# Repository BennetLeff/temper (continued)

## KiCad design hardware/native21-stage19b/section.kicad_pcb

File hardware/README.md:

# Current Temper hardware

The current engineering candidate is **native-21 stage19b**, the full-bridge
power stage. Open [the pinned KiCad project](native21-stage19b/section.kicad_pro).
It is a **digital candidate, not a fabrication or mains-operation release**.

Before a current-design review, run:

```sh
make hardware-baseline-check
sh scripts/check_hardware_baseline.sh --board hardware/native21-stage19b/section.kicad_pcb
```

[CURRENT.tsv](CURRENT.tsv) pins the exact board, schematic, project, rules,
libraries, source inputs and source evidence. The Rust guard rejects missing,
changed, malformed or ambiguous inputs and any selected board whose full hash
differs. A successful check establishes identity only. It does not certify the
design or prove that an edited producer worktree still matches this snapshot.

| Identity | Value |
|---|---|
| Board SHA-256 | `b19a45530bb0f39d2d3c0412e3774b6d5a47c4238d3fee867790cce410756662` |
| Authored copper (`provenance/copper.json`) | `ce49f20024545fe28f104e72f69c0d1362227a15145b3a1c3bd4b915199b6cf2`, the reproducible identity: rebuilds of the same copper differ in KiCad UUIDs and timestamps |
| Schematic | `e6993fa4abab0a845d1cc0d07074c39ab9f536eca6f864dae993d76941ae8d35` |
| Frozen netlist (`provenance/default.net`) | `8a7e1c4a869445d7d11ab9ee4c69f0dc40207cf4f06463a0ac8b2238cffef92b` |
| Stage 19b hardware commit | `5d53896c3` on `codex/power-stage-integration` (tag `native21s19b`; 357 parts). Carries stage 17b (Bourns CSS2H R5), stage 18 (RES_A 12.6 mm outer-layer spacing) and stage 19 (review N1/K6 bypass and DRC fixes from `365151b62`, PI1/PI2 local caps at U41/U42/U26, SI1/SI2 return paths, C153–C156) |
| Superseded | stage15b `9a9c43c6…` (hardware commit `d5b1e9995504f1ee7b6439a57f998d73125b3352`), stage 16 `e9481ed6…`, stage 17b `96501e7d…`, the integration stage 18 `3768a126…`, and the review-fix side builds `dadcaad3…` and `98fa8bee…` (branches `claude/native21-stage17-review` / `claude/native21-stage18-review`, folded into stage 19); the guard rejects all of them |

## Source ownership and updates

The source owner is branch `codex/power-stage-integration`, unit
`zapote/power-stage-120v/`; stage 19b is merged there at `5d53896c3`. Atopile entry:
`elec/src/power_stage_120v.ato:PowerStage120V`. Its `native-21/layout/copper.json`
and `native-21/verification/final-manifest.json` define the routed candidate.
Do not edit this snapshot to make a check pass. Make design changes in the
owning sources, regenerate and review them, then deliberately publish a new
snapshot and update CURRENT.tsv together, retaining the previous identity here.
Compare live producer source hashes to the snapshot before reusing its results.

The routed board was built from the committed `copper.json` by
`sh native-21/layout/incr_iter.sh native-21/layout/copper.json - OUTDIR`
(`native-21/layout/gates/chain.sh`). Its `source/` directory is provenance, not a
second editable source of truth.

## Superseded inputs and filename traps

| Location | Status |
|---|---|
| Legacy half-bridge `pcb/`, root `elec/` | Removed from main on 2026-10-08; recoverable from tag `archive/temper-legacy-2026-10-08`. Never the current design |
| `native-21/section.kicad_pcb` in the producer | Placement-only build input, not the routed board |
| `native-21/routed/section.kicad_pcb` in the producer | Stale October 7 output; not stage19b |
| Enclosure `inputs/native-21/` snapshots | Independently versioned; check the hash before reuse (R38's was stage12) |
| Stage15b through stage 18 boards, the review-fix side builds, and the engineering review's findings | The review (`output/engineering-review-native21-stage15b-2026-10-11/REPORT.md`) names stage15b; its addendum covers the side build. Stage 19's results are in `zapote/power-stage-120v/DECISIONS.md` item 19 at `5d53896c3` |

Do not transfer component references, topology, spacing limits, firmware
thresholds or a readiness verdict between these designs. All future reports
must name the manifest and full selected PCB hash before interpreting findings.

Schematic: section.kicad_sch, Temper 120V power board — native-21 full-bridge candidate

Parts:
BR1: GBJ2510-F; Diode_Bridge_GBJ2510
C1, C2: R463N410050N1K; KEMET_R463N410000N1M_P22.50_ReviewOnly
C3, C4: DE1E3RA222MA4BP01F; Murata_DE1E3RA222MA4BP01F_P10.0_Pad1.5_ReviewOnly
C5, C6: B32676G1905K000; TDK_B32656G0275J000_4Pin_P37.50_P20.30_ReviewOnly
C7, C14, C25, C28, C29, C32, C34, C35, C36, C37, C44, C45, C46, C47, C48, C49, C54, C61, C65, C70, C74, C75, C80, C81, C82, C87, C88, C89, C131, C133, C134, C135, C137, C138, C139, C141, C142, C144, C153, C154, C155, C156: CC0603KRX7R9BB104; C_0603_1608Metric
C8, C10, C15, C17: CC0805KRX7R9BB104; C_0805_2012Metric
C9, C16, C24, C26, C90, C91, C92, C93, C94, C95, C96, C97, C98, C99, C100, C102, C103, C104, C106, C107, C108, C132, C136, C140: UMK325AB7106KM-T; C_1210_3225Metric
C11, C18: GRM21BZ71E106KE15L; C_0805_2012Metric
C12, C13, C19, C20: GRM31A5C3A102JW01D; C_1206_3216Metric
C21, C22, C23, C151, C152: B32654A1104K000; TDK_B32654_P27.5_W14.0_L31.5_Radial
C27, C31, C33, C55, C56, C62, C63, C66, C67, C68, C69, C76, C77, C78, C79, C83, C84, C85, C86, C143: C0603C102J5GACTU; C_0603_1608Metric
C30: CL10C101JB8NNNC; C_0603_1608Metric
C38, C39, C40, C41: B32652A0104K000; TDK_B32652A0104K000_P15.00_ReviewOnly
C42, C43: GRM31C5C1H104JA01L; C_1206_3216Metric
C50, C51, C52, C53, C57, C58, C59, C60, C64: GRM188R71E105KA12D; C_0603_1608Metric
C71, C72, C105, C109: CL10C331JB8NNNC; C_0603_1608Metric
C110, C111, C112, C113, C114, C115, C116, C117, C118, C119, C120, C121, C122, C123, C124, C125: CL05B104KB54PNC; C_0402_1005Metric
C126, C127, C128, C129: 6SVPC220M; CP_Elec_6.3x5.9
C145, C146, C147, C148, C149, C150: CL21B105KBFNNNE; C_0805_2012Metric
D3, D17: 30KPA150CA; P600_Axial_P12.70mm_ReviewOnly
D4, D5: BAS116H,115; D_SOD-123F
D6, D7, D8, D9: PMEG6030EP,115; D_SOD-128
D14, D15, D16: 1N4148W; D_SOD-123
F1: KLDR025.TXP; Fuseholder_Clip-10.3x38mm_Littelfuse_125_Inline_P41.76x10.8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
F2: 3403.0171; Fuse_Schurter_UMT250
J1: 1711725; TerminalBlock_Phoenix_MKDS-3-2-5.08_1x02_P5.08mm_Horizontal
J2, J5, J7, J8, J9, J10: 74650074; Wuerth_REDCUBE-THR_WP-THRBU_74650074_THR
J3, J11: B2P3-VH(LF)(SN); JST_VH_B2P3-VH_1x02_P7.92mm_Vertical
J4: 0430451612; Molex_Micro-Fit_3.0_43045-1612_2x08_P3.00mm_Vertical
J6: 1704004; Phoenix_KDS3_1704004_1Pos_2Pin_ReviewOnly
L1: B82726S2203A020; B82726S2_ReviewOnly
PS1: IRM-20-15; Converter_ACDC_MeanWell_IRM-20-xx_THT
PS2: IRM-20-24; Converter_ACDC_MeanWell_IRM-20-xx_THT
Q1, Q4: AO3400A; SOT-23
Q2, Q3, Q5, Q6: IPW65R018CFD7; TO-247-3_Vertical
Q7, Q8, Q9: MMBT3904; SOT-23
R1, R2: 1206W4F1003T5E; R_1206_3216Metric
R3, R4: RC1206FR-07220KL; R_1206_3216Metric
R5: CSS2H-2512R-1L00F; R_Shunt_Bourns_CSS2H-2512_Kelvin
R6, R14: 0603WAF1000T5E; R_0603_1608Metric
R7, R15, R62, R128: 0603WAF1003T5E; R_0603_1608Metric
R8, R16: 0603WAF3300T5E; R_0603_1608Metric
R9, R17: RT0603BRD0749K9L; R_0603_1608Metric
R10, R12, R18, R20: RC1206FR-073R9L; R_1206_3216Metric
R11, R13, R19, R21, R73, R76, R90, R91, R108, R109, R123, R124, R126: 0603WAF1002T5E; R_0603_1608Metric
R22, R23, R24, R25, R26, R27, R28, R29: RC1206FR-07470KL; R_1206_3216Metric
R30: RT0603BRD0715K8L; R_0603_1608Metric
R31: 0603WAF5601T5E; R_0603_1608Metric
R32, R33, R36, R44, R45, R49, R50, R78, R79, R80, R82, R84, R86, R88, R96, R97, R98, R100, R102, R104, R106, R111, R112, R113, R115, R117, R119, R121: RT0603BRD0710KL; R_0603_1608Metric
R34: RT0603BRD0712K6L; R_0603_1608Metric
R35: TNPW060311K7BEEA; R_0603_1608Metric
R37: RT0603BRD07140KL; R_0603_1608Metric
R38: 0603WAF0000T5E; R_0603_1608Metric
R39: RC1206FR-071R5L; R_1206_3216Metric
R40, R41: RT0603BRD071KL; R_0603_1608Metric
R42: 1206W4F1001T5E; R_1206_3216Metric
R43, R46: RT0603BRD072K21L; R_0603_1608Metric
R47, R89, R107, R122: 0603WAF1001T5E; R_0603_1608Metric
R48: RT0603BRD07105KL; R_0603_1608Metric
R51, R52, R55, R56: RL1206FR-070R68L; R_1206_3216Metric
R53, R54, R57, R58: 1206W4F100KT5E; R_1206_3216Metric
R59, R63, R65: RC1206FR-072K2L; R_1206_3216Metric
R61, R93: RT0603BRD0711KL; R_0603_1608Metric
R67, R68, R69, R70: RC1206FR-0716K5L; R_1206_3216Metric
R71, R72, R74, R75: 0603WAF4991T5E; R_0603_1608Metric
R77, R95, R110: RT0603BRD076K2L; R_0603_1608Metric
R81, R99, R114: RT0603BRD074K42L; R_0603_1608Metric
R83, R101, R116: RT0603BRD077K68L; R_0603_1608Metric
R85, R103, R118: RT0603BRD07120KL; R_0603_1608Metric
R87, R105, R120: ARG03BTC1333; R_0603_1608Metric
R92, R94: RT0603BRD0763K4L; R_0603_1608Metric
R125: 0603WAF3302T5E; R_0603_1608Metric
R127, R129: 0603WAF2702T5E; R_0603_1608Metric
RV1: TMOV20RP175E; TMOV20RP_ReviewOnly
T1: CST3015-100ED; CST3015
U1, U2: UCC21550BDWKR; SOIC16W_Isolated
U3, U37, U38, U39: TPS70950DBVR; SOT-23-5
U4: AMC1311BDWVR; SOIC-8_7.5x5.85mm_P1.27mm
U5: LM4040A25IDBZR; SOT-23
U6, U7, U10, U11, U12: TLV3201AIDBVR; SOT-23-5
U8: SN74LVC1G10DBVR; SOT-23-6
U9, U32, U33, U34: ISO7710DWR; SOIC16W_DW0016B_HV
U13, U25: SN74LVC1G332DBVR; SOT-23-6
U14: TPS3700DDCR; SOT-23-6
U15, U24, U40: SN74LVC1G17DBVR; SOT-23-5
U16, U18, U20: TLVH431BQDBZR; SOT-23
U17, U19, U21: TL431AIDBZR; SOT-23
U22, U23: SN74LVC1G32DBVR; SOT-23-5
U26: TPS7A4700RGWR; Texas_RGW0020A_VQFN-20-1EP_5x5mm_P0.65mm_EP3.15x3.15mm
U29, U30, U31: LM339BIDR; SOIC-14_3.9x8.7mm_P1.27mm
U36: VOL628A-3X001T; VOL628A_LSOP4_ReviewOnly
U41, U42: R24C2T25/R-R; RECOM_SSOP-36_7.5x12.83mm_P0.65mm_ReviewOnly

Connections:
ac_l_in: F1.1 (p1), J1.1 (p1)
ac_n_in: C1.2 (p2), J1.2 (p2), L1.2 (b_in), R2.2 (p2), RV1.2 (p2)
bias_bad: U22.2 (B), U23.2 (B), U40.4 (Y); also elsewhere on the board
bias_bad_flt: C143.1 (p1), R126.2 (p2), U40.2 (A)
bias_bad_raw: R126.1 (p1), U25.4 (Y)
bias_ha-en: R62.2 (p2), R127.1 (p1), U41.4 (p4)
bias_ha-fbm: C71.1 (p1), R92.2 (p2), R93.1 (p1), U41.33 (p33), U41.34 (p34)
bias_ha.iso-p3: U41.3 (p3)
bias_ha.iso-p32: U41.32 (p32)
bias_ha.monitor-base: D15.1 (p1), Q8.1 (p1), R108.1 (p1)
bias_ha.monitor-good: D15.2 (p2), R107.2 (p2), U30.1 (OUT2), U30.2 (OUT1), U30.13 (OUT4), U30.14 (OUT3)
bias_ha.monitor-halfref: R97.2 (p2), R98.1 (p1), U30.5 (IN1+), U30.6 (IN2-), U30.8 (IN3-), U30.11 (IN4+)
bias_ha.monitor-isoin: Q8.3 (p3), R109.2 (p2), U33.4 (IN)
bias_ha.monitor-ov: C77.1 (p1), R101.2 (p2), R102.1 (p1), U30.4 (IN1-)
bias_ha.monitor-ref: R63.2 (p2), R97.1 (p1), R107.1 (p1), U19.1 (K), U19.2 (REF)
bias_ha.monitor-spanov: C79.1 (p1), R105.2 (p2), R106.1 (p1), U30.10 (IN4-)
bias_ha.monitor-spanuv: C78.1 (p1), R103.2 (p2), R104.1 (p1), U30.9 (IN3+)
bias_ha.monitor-uv: C76.1 (p1), R99.2 (p2), R100.1 (p1), U30.7 (IN2+)
bias_ha.monitor-v5: C136.1 (p1), C137.1 (p1), R109.1 (p1), U33.3 (VCC1), U38.5 (OUT)
bias_ha.monitor.iso-nc2: U33.2 (NC2)
bias_ha.monitor.iso-nc5: U33.5 (NC5)
bias_ha.monitor.iso-nc6: U33.6 (NC6)
bias_ha.monitor.iso-nc8: U33.8 (NC8)
bias_ha.monitor.iso-nc10: U33.10 (NC10)
bias_ha.monitor.iso-nc11: U33.11 (NC11)
bias_ha.monitor.iso-nc12: U33.12 (NC12)
bias_ha.monitor.iso-nc15: U33.15 (NC15)
bias_ha.monitor.ldo5-nc: U38.4 (NC)
bias_ha.split-fb: R95.2 (p2), R96.1 (p1), U18.1 (REF)
bias_ha_bad: U25.3 (B), U33.13 (OUT)
bias_hb-en: R128.2 (p2), R129.1 (p1), U42.4 (p4)
bias_hb-fbm: C72.1 (p1), R61.1 (p1), R94.2 (p2), U42.33 (p33), U42.34 (p34)
bias_hb.iso-p3: U42.3 (p3)
bias_hb.iso-p32: U42.32 (p32)
bias_hb.monitor-base: D16.1 (p1), Q9.1 (p1), R123.1 (p1)
bias_hb.monitor-good: D16.2 (p2), R122.2 (p2), U31.1 (OUT2), U31.2 (OUT1), U31.13 (OUT4), U31.14 (OUT3)
bias_hb.monitor-halfref: R112.2 (p2), R113.1 (p1), U31.5 (IN1+), U31.6 (IN2-), U31.8 (IN3-), U31.11 (IN4+)
bias_hb.monitor-isoin: Q9.3 (p3), R124.2 (p2), U34.4 (IN)
bias_hb.monitor-ov: C84.1 (p1), R116.2 (p2), R117.1 (p1), U31.4 (IN1-)
bias_hb.monitor-ref: R65.2 (p2), R112.1 (p1), R122.1 (p1), U21.1 (K), U21.2 (REF)
bias_hb.monitor-spanov: C86.1 (p1), R120.2 (p2), R121.1 (p1), U31.10 (IN4-)
bias_hb.monitor-spanuv: C85.1 (p1), R118.2 (p2), R119.1 (p1), U31.9 (IN3+)
bias_hb.monitor-uv: C83.1 (p1), R114.2 (p2), R115.1 (p1), U31.7 (IN2+)
bias_hb.monitor-v5: C140.1 (p1), C141.1 (p1), R124.1 (p1), U34.3 (VCC1), U39.5 (OUT)
bias_hb.monitor.iso-nc2: U34.2 (NC2)
bias_hb.monitor.iso-nc5: U34.5 (NC5)
bias_hb.monitor.iso-nc6: U34.6 (NC6)
bias_hb.monitor.iso-nc8: U34.8 (NC8)
bias_hb.monitor.iso-nc10: U34.10 (NC10)
bias_hb.monitor.iso-nc11: U34.11 (NC11)
bias_hb.monitor.iso-nc12: U34.12 (NC12)
bias_hb.monitor.iso-nc15: U34.15 (NC15)
bias_hb.monitor.ldo5-nc: U39.4 (NC)
bias_hb.split-fb: R110.2 (p2), R111.1 (p1), U20.1 (REF)
bias_hb_bad: U25.6 (C), U34.13 (OUT)
bias_ls-fb: R77.2 (p2), R78.1 (p1), U16.1 (REF)
bias_ls_bad: U25.1 (A), U32.13 (OUT)
blw_l: F2.2 (p2), J11.1 (p1)
bus_fault: J4.10 (p10), U13.4 (Y); also elsewhere on the board
bus_fault_hot: U8.4 (Y), U9.4 (IN); also elsewhere on the board
bus_fault_iso: U9.13 (OUT), U13.1 (A)
bus_p: C5.1 (p1), C5.2 (p2), C6.1 (p1), C6.2 (p2), C12.1 (p1), C19.1 (p1), C38.1 (p1), C39.1 (p1), C40.1 (p1), C41.1 (p1), D3.1 (p1), J8.1, Q2.2 (D), Q5.2 (D), R3.1 (p1), R26.1 (p1)
busbleed_mid: D3.2 (p2), D17.1 (p1), R3.2 (p2), R4.1 (p1)
coil_feed: J2.1, T1.2
crbleed_1: R22.2 (p2), R23.1 (p1)
crbleed_2: R23.2 (p2), R24.1 (p1)
crbleed_3: R24.2 (p2), R25.1 (p1)
ct_mon: J4.14 (p14), R47.2 (p2); also elsewhere on the board
ct_oc_neg: U11.1 (OUT), U13.6 (C)
ct_oc_pos: U10.1 (OUT), U13.3 (B)
ct_ref_hi: R43.2 (p2), R44.1 (p1), U10.4 (INN)
ct_ref_lo: R45.2 (p2), R46.1 (p1), U11.3 (INP)
ct_s1: C42.1 (p1), R39.1 (p1), R42.1 (p1), T1.3 (S1)
ct_s2: C42.2 (p2), C43.1 (p1), R39.2 (p2), R40.2 (p2), R41.1 (p1), T1.4 (S2), U12.4 (INN)
ct_sense_mon: D4.2 (A), D5.1 (K), R42.2 (p2), R47.1 (p1), U10.3 (INP), U11.4 (INN), U12.3 (INP)
ct_zc: J4.13 (p13), U12.1 (OUT); also elsewhere on the board
hot5: C26.1 (p1), C28.1 (p1), C32.1 (p1), C34.1 (p1), C35.1 (p1), C36.1 (p1), C49.1 (p1), C149.1 (p1), R31.1 (p1), R48.1 (p1), R50.1 (p1), U3.5 (OUT), U4.1 (VDD1), U6.5 (VCC), U7.5 (VCC), U8.5 (VCC), U9.3 (VCC1), U15.5 (VCC); also elsewhere on the board
hot5_ok_hot: U8.6 (C), U15.4 (Y)
hot5_uv_raw: R50.2 (p2), U14.1 (OUTA), U15.2 (A)
hot5_uv_sense: R48.2 (p2), R49.1 (p1), U14.3 (INA)
hv_ret: C5.3 (p3), C5.4 (p4), C6.3 (p3), C6.4 (p4), C38.2 (p2), C39.2 (p2), C40.2 (p2), C41.2 (p2), D17.2 (p2), J10.1, R4.2 (p2), R5.4 (p4)
l_f: C1.1 (p1), F1.2 (p2), L1.1 (a_in), R1.1 (p1), RV1.1 (p1)
l_filt: BR1.2 (AC1), C2.1 (p1), C3.1 (p1), F2.1 (p1), J3.1 (p1), L1.4 (a_out), PS1.1 (ACL), R67.1 (p1)
ldo_nr: C64.1 (p1), U26.14 (p14)
led1: R68.2 (p2), U36.1 (AC1)
led2: R69.1 (p1), U36.2 (AC2)
leg_a-dis: Q1.3 (D), R8.1 (p1), U22.1 (A)
leg_a-driver_dis: R73.2 (p2), U1.5 (DIS), U22.4 (Y)
leg_a-gate_h: C55.1 (p1), D6.2 (p2), Q2.1 (G), R10.2 (p2), R11.1 (p1)
leg_a-gate_l: C56.1 (p1), D7.2 (p2), Q3.1 (G), R12.2 (p2), R13.1 (p1)
leg_a-off_h: D6.1 (p1), R53.1 (p1)
leg_a-off_l: D7.1 (p1), R54.1 (p1)
leg_a-out_h: R10.1 (p1), R53.2 (p2), U1.15 (OUTA)
leg_a-out_l: R12.1 (p1), R54.2 (p2), U1.10 (OUTB); also elsewhere on the board
leg_a-permit_gate: Q1.1 (G), R6.2 (p2), R7.1 (p1)
leg_a.bias_h-damp: C126.1 (p1), R51.2 (p2)
leg_a.bias_l-damp: C127.1 (p1), R52.2 (p2)
leg_a.driver-dt: R9.1 (p1), U1.6 (DT)
leg_a.driver-nc_7: U1.7 (NC_7)
leg_b-dis: Q4.3 (D), R16.1 (p1), U23.1 (A)
leg_b-driver_dis: R76.2 (p2), U2.5 (DIS), U23.4 (Y)
leg_b-gate_h: C62.1 (p1), D8.2 (p2), Q5.1 (G), R18.2 (p2), R19.1 (p1)
leg_b-gate_l: C63.1 (p1), D9.2 (p2), Q6.1 (G), R20.2 (p2), R21.1 (p1)
leg_b-off_h: D8.1 (p1), R57.1 (p1)
leg_b-off_l: D9.1 (p1), R58.1 (p1)
leg_b-out_h: R18.1 (p1), R57.2 (p2), U2.15 (OUTA)
leg_b-out_l: R20.1 (p1), R58.2 (p2), U2.10 (OUTB)
leg_b-permit_gate: Q4.1 (G), R14.2 (p2), R15.1 (p1)
leg_b.bias_h-damp: C128.1 (p1), R55.2 (p2)
leg_b.bias_l-damp: C129.1 (p1), R56.2 (p2)
leg_b.driver-dt: R17.1 (p1), U2.6 (DT)
leg_b.driver-nc_7: U2.7 (NC_7)
leg_ret: C13.2 (p2), C20.2 (p2), C52.1 (p1), C53.1 (p1), C56.2 (p2), C59.1 (p1), C60.1 (p1), C63.2 (p2), C92.1 (p1), C93.1 (p1), C96.1 (p1), C97.1 (p1), C114.1 (p1), C115.1 (p1), C116.1 (p1), C117.1 (p1), C122.1 (p1), C123.1 (p1), C124.1 (p1), C125.1 (p1), Q3.3 (S), Q6.3 (S), R5.1 (p1), R13.2 (p2), R21.2 (p2), R52.1 (p1), R56.1 (p1), R72.2 (p2), R75.2 (p2), R77.1 (p1), R81.1 (p1), R83.1 (p1), U16.2 (K); also elsewhere on the board
line_zc: J4.16 (p16), U24.4 (Y)
line_zc.buffer-nc: U24.1 (NC)
line_zc_raw: R125.2 (p2), U24.2 (A), U36.4 (C)
monitor_ls-base: D14.1 (p1), Q7.1 (p1), R90.1 (p1)
monitor_ls-good: D14.2 (p2), R89.2 (p2), U29.1 (OUT2), U29.2 (OUT1), U29.13 (OUT4), U29.14 (OUT3)
monitor_ls-halfref: R79.2 (p2), R80.1 (p1), U29.5 (IN1+), U29.6 (IN2-), U29.8 (IN3-), U29.11 (IN4+)
monitor_ls-isoin: Q7.3 (p3), R91.2 (p2), U32.4 (IN)
monitor_ls-ov: C67.1 (p1), R83.2 (p2), R84.1 (p1), U29.4 (IN1-)
monitor_ls-ref: R59.2 (p2), R79.1 (p1), R89.1 (p1), U17.1 (K), U17.2 (REF)
monitor_ls-spanov: C69.1 (p1), R87.2 (p2), R88.1 (p1), U29.10 (IN4-)
monitor_ls-spanuv: C68.1 (p1), R85.2 (p2), R86.1 (p1), U29.9 (IN3+)
monitor_ls-uv: C66.1 (p1), R81.2 (p2), R82.1 (p1), U29.7 (IN2+)
monitor_ls-v5: C132.1 (p1), C133.1 (p1), R91.1 (p1), U32.3 (VCC1), U37.5 (OUT)
monitor_ls.iso-nc2: U32.2 (NC2)
monitor_ls.iso-nc5: U32.5 (NC5)
monitor_ls.iso-nc6: U32.6 (NC6)
monitor_ls.iso-nc8: U32.8 (NC8)
monitor_ls.iso-nc10: U32.10 (NC10)
monitor_ls.iso-nc11: U32.11 (NC11)
monitor_ls.iso-nc12: U32.12 (NC12)
monitor_ls.iso-nc15: U32.15 (NC15)
monitor_ls.ldo5-nc: U37.4 (NC)
n_filt: BR1.3 (AC2), C2.2 (p2), C4.1 (p1), J11.2 (p2), L1.3 (b_out), PS1.2 (ACN), PS2.2 (ACN), R70.2 (p2)
n_ha: C10.2 (p2), C11.2 (p2), C50.2 (p2), C51.2 (p2), C71.2 (p2), C75.2 (p2), C76.2 (p2), C77.2 (p2), C78.2 (p2), C79.2 (p2), C80.2 (p2), C90.2 (p2), C91.2 (p2), C104.2 (p2), C110.2 (p2), C111.2 (p2), C112.2 (p2), C113.2 (p2), C126.2 (p2), C135.2 (p2), C136.2 (p2), C137.2 (p2), C145.2 (p2), Q8.2 (p2), R93.2 (p2), R96.2 (p2), R98.2 (p2), R100.2 (p2), R102.2 (p2), R104.2 (p2), R106.2 (p2), R108.2 (p2), U1.14 (VSSA), U18.3 (A), U19.3 (A), U30.12 (GND), U33.1 (GND1), U33.7 (GND1B), U38.2 (GND), U41.19 (p19), U41.20 (p20), U41.21 (p21), U41.22 (p22), U41.23 (p23), U41.24 (p24), U41.25 (p25), U41.26 (p26), U41.27 (p27), U41.30 (p30), U41.31 (p31), U41.35 (p35), U41.36 (p36); also elsewhere on the board
n_hb: C17.2 (p2), C18.2 (p2), C57.2 (p2), C58.2 (p2), C72.2 (p2), C82.2 (p2), C83.2 (p2), C84.2 (p2), C85.2 (p2), C86.2 (p2), C87.2 (p2), C94.2 (p2), C95.2 (p2), C108.2 (p2), C118.2 (p2), C119.2 (p2), C120.2 (p2), C121.2 (p2), C128.2 (p2), C139.2 (p2), C140.2 (p2), C141.2 (p2), C147.2 (p2), Q9.2 (p2), R61.2 (p2), R111.2 (p2), R113.2 (p2), R115.2 (p2), R117.2 (p2), R119.2 (p2), R121.2 (p2), R123.2 (p2), U2.14 (VSSA), U20.3 (A), U21.3 (A), U31.12 (GND), U34.1 (GND1), U34.7 (GND1B), U39.2 (GND), U42.19 (p19), U42.20 (p20), U42.21 (p21), U42.22 (p22), U42.23 (p23), U42.24 (p24), U42.25 (p25), U42.26 (p26), U42.27 (p27), U42.30 (p30), U42.31 (p31), U42.35 (p35), U42.36 (p36); also elsewhere on the board
n_ls: C8.2 (p2), C9.2 (p2), C15.2 (p2), C16.2 (p2), C24.2 (p2), C52.2 (p2), C53.2 (p2), C59.2 (p2), C60.2 (p2), C64.2 (p2), C65.2 (p2), C66.2 (p2), C67.2 (p2), C68.2 (p2), C69.2 (p2), C70.2 (p2), C74.2 (p2), C81.2 (p2), C92.2 (p2), C93.2 (p2), C96.2 (p2), C97.2 (p2), C98.2 (p2), C99.2 (p2), C100.2 (p2), C102.2 (p2), C103.2 (p2), C105.2 (p2), C106.2 (p2), C107.2 (p2), C109.2 (p2), C114.2 (p2), C115.2 (p2), C116.2 (p2), C117.2 (p2), C122.2 (p2), C123.2 (p2), C124.2 (p2), C125.2 (p2), C127.2 (p2), C129.2 (p2), C131.2 (p2), C132.2 (p2), C133.2 (p2), C146.2 (p2), C148.2 (p2), PS2.3 (VN), Q7.2 (p2), R78.2 (p2), R80.2 (p2), R82.2 (p2), R84.2 (p2), R86.2 (p2), R88.2 (p2), R90.2 (p2), R127.2 (p2), R129.2 (p2), U1.9 (VSSB), U2.9 (VSSB), U16.3 (A), U17.3 (A), U26.4 (p4), U26.5 (p5), U26.7 (p7), U26.8 (p8), U26.9 (p9), U26.10 (p10), U26.21 (p21), U29.12 (GND), U32.1 (GND1), U32.7 (GND1B), U37.2 (GND), U41.1 (p1), U41.2 (p2), U41.5 (p5), U41.8 (p8), U41.9 (p9), U41.10 (p10), U41.11 (p11), U41.12 (p12), U41.13 (p13), U41.14 (p14), U41.15 (p15), U41.16 (p16), U41.17 (p17), U41.18 (p18), U42.1 (p1), U42.2 (p2), U42.5 (p5), U42.8 (p8), U42.9 (p9), U42.10 (p10), U42.11 (p11), U42.12 (p12), U42.13 (p13), U42.14 (p14), U42.15 (p15), U42.16 (p16), U42.17 (p17), U42.18 (p18); also elsewhere on the board
ocp_kelvin_n: R5.3 (p3), R33.2 (p2)
ocp_kelvin_p: C25.2 (p2), C26.2 (p2), C27.2 (p2), C28.2 (p2), C30.2 (p2), C31.2 (p2), C32.2 (p2), C33.2 (p2), C34.2 (p2), C35.2 (p2), C36.2 (p2), C48.2 (p2), C49.2 (p2), C149.2 (p2), R5.2 (p2), R30.2 (p2), R35.2 (p2), R37.2 (p2), R49.2 (p2), U3.2 (GND), U4.3 (SHTDN), U4.4 (GND1), U5.2 (A), U6.2 (GND), U7.2 (GND), U8.2 (GND), U9.1 (GND1), U9.7 (GND1B), U14.2 (GND), U14.4 (INB), U15.3 (GND); also elsewhere on the board
ocp_node: C30.1 (p1), R32.2 (p2), R33.1 (p1), U6.3 (INP); also elsewhere on the board
ocp_ok_hot: U6.1 (OUT), U8.1 (A)
ocp_thresh: C31.1 (p1), R34.2 (p2), R35.1 (p1), U6.4 (INN)
outb: U14.6 (OUTB)
ovp_ok_hot: U7.1 (OUT), U8.3 (B)
ovp_thresh: C33.1 (p1), R36.2 (p2), R37.1 (p1), U7.3 (INP)
p2: U26.2 (p2)
p6: U26.6 (p6)
p11: U26.11 (p11)
p12: U26.12 (p12)
p17: U26.17 (p17)
p18: U26.18 (p18)
p19: U26.19 (p19)
p_ha: C10.1 (p1), C11.1 (p1), C75.1 (p1), C80.1 (p1), C104.1 (p1), C135.1 (p1), C145.1 (p1), R63.1 (p1), R71.1 (p1), R92.1 (p1), R103.1 (p1), R105.1 (p1), U1.16 (VDDA), U30.3 (VCC), U38.1 (IN), U38.3 (EN), U41.28 (p28), U41.29 (p29); also elsewhere on the board
p_hb: C17.1 (p1), C18.1 (p1), C82.1 (p1), C87.1 (p1), C108.1 (p1), C139.1 (p1), C147.1 (p1), R65.1 (p1), R74.1 (p1), R94.1 (p1), R118.1 (p1), R120.1 (p1), U2.16 (VDDA), U31.3 (VCC), U39.1 (IN), U39.3 (EN), U42.28 (p28), U42.29 (p29); also elsewhere on the board
pe: C3.2 (p2), C4.2 (p2), J6.1 (p1), J6.2 (p2), R38.1 (p1)
permit: J4.9 (p9), R6.1 (p1), R14.1 (p1); also elsewhere on the board
pwm_ha: J4.5 (p5), U1.1 (INA); also elsewhere on the board
pwm_hb: J4.7 (p7), U2.1 (INA); also elsewhere on the board
pwm_la: J4.6 (p6), U1.2 (INB); also elsewhere on the board
pwm_lb: J4.8 (p8), U2.2 (INB)
r1mid: R67.2 (p2), R68.1 (p1)
r2mid: R69.2 (p2), R70.1 (p1)
rect_n: BR1.4 (MINUS), J9.1
rect_p: BR1.1 (PLUS), J7.1
ref25: R31.2 (p2), R32.1 (p1), R34.1 (p1), R36.1 (p1), U5.1 (K)
res_a: C21.1 (p1), C22.1 (p1), C23.1 (p1), C151.1 (p1), C152.1 (p1), J5.1, R22.1 (p1)
selv_gnd: C7.2 (p2), C14.2 (p2), C29.2 (p2), C37.2 (p2), C43.2 (p2), C44.2 (p2), C45.2 (p2), C46.2 (p2), C47.2 (p2), C54.2 (p2), C61.2 (p2), C88.2 (p2), C89.2 (p2), C134.2 (p2), C138.2 (p2), C142.2 (p2), C143.2 (p2), C144.2 (p2), C150.2 (p2), C153.2 (p2), C154.2 (p2), C155.2 (p2), C156.2 (p2), D5.2 (A), J4.2 (p2), J4.4 (p4), J4.15 (p15), PS1.3 (VN), Q1.2 (S), Q4.2 (S), R7.2 (p2), R9.2 (p2), R15.2 (p2), R17.2 (p2), R38.2 (p2), R41.2 (p2), R44.2 (p2), R46.2 (p2), U1.4 (GNDI), U2.4 (GNDI), U4.5 (GND2), U9.9 (GND2), U9.16 (GND2B), U10.2 (GND), U11.2 (GND), U12.2 (GND), U13.2 (GND), U22.3 (GND), U23.3 (GND), U24.3 (GND), U25.2 (GND), U32.9 (GND2), U32.16 (GND2B), U33.9 (GND2), U33.16 (GND2B), U34.9 (GND2), U34.16 (GND2B), U36.3 (E), U40.3 (GND); also elsewhere on the board
sw_a: C12.2 (p2), C13.1 (p1), C50.1 (p1), C51.1 (p1), C55.2 (p2), C90.1 (p1), C91.1 (p1), C110.1 (p1), C111.1 (p1), C112.1 (p1), C113.1 (p1), Q2.3 (S), Q3.2 (D), R11.2 (p2), R51.1 (p1), R71.2 (p2), R95.1 (p1), R99.1 (p1), R101.1 (p1), T1.1, U18.2 (K); also elsewhere on the board
sw_b: C19.2 (p2), C20.1 (p1), C21.2 (p2), C22.2 (p2), C23.2 (p2), C57.1 (p1), C58.1 (p1), C62.2 (p2), C94.1 (p1), C95.1 (p1), C118.1 (p1), C119.1 (p1), C120.1 (p1), C121.1 (p1), C151.2 (p2), C152.2 (p2), Q5.3 (S), Q6.2 (D), R19.2 (p2), R25.2 (p2), R55.1 (p1), R74.2 (p2), R110.1 (p1), R114.1 (p1), R116.1 (p1), U20.2 (K); also elsewhere on the board
tco_l: J3.2 (p2), PS2.1 (ACL)
u_bias_flt-nc: U40.1 (NC)
u_hot5_schmitt-nc: U15.1 (NC)
u_iso-nc2: U9.2 (NC2)
u_iso-nc5: U9.5 (NC5)
u_iso-nc6: U9.6 (NC6)
u_iso-nc8: U9.8 (NC8)
u_iso-nc10: U9.10 (NC10)
u_iso-nc11: U9.11 (NC11)
u_iso-nc12: U9.12 (NC12)
u_iso-nc15: U9.15 (NC15)
u_ldo-nc: U3.4 (NC)
u_ref-nc: U5.3 (NC)
v3v3: C7.1 (p1), C14.1 (p1), C29.1 (p1), C37.1 (p1), C44.1 (p1), C45.1 (p1), C46.1 (p1), C47.1 (p1), C54.1 (p1), C61.1 (p1), C88.1 (p1), C89.1 (p1), C134.1 (p1), C138.1 (p1), C142.1 (p1), C144.1 (p1), C150.1 (p1), C153.1 (p1), C154.1 (p1), C155.1 (p1), C156.1 (p1), D4.1 (K), J4.3 (V3V3_FROM_CONTROLLER), R8.2 (p2), R16.2 (p2), R40.1 (p1), R43.1 (p1), R45.1 (p1), R73.1 (p1), R76.1 (p1), R125.1 (p1), U1.3 (VCCI_1), U1.8 (VCCI_2), U2.3 (VCCI_1), U2.8 (VCCI_2), U4.8 (VDD2), U9.14 (VCC2), U10.5 (VCC), U11.5 (VCC), U12.5 (VCC), U13.5 (VCC), U22.5 (VCC), U23.5 (VCC), U24.5 (VCC), U25.5 (VCC), U32.14 (VCC2), U33.14 (VCC2), U34.14 (VCC2), U40.5 (VCC); also elsewhere on the board
v15_ls: C8.1 (p1), C9.1 (p1), C15.1 (p1), C16.1 (p1), C24.1 (p1), C25.1 (p1), C48.1 (p1), C65.1 (p1), C70.1 (p1), C99.1 (p1), C100.1 (p1), C131.1 (p1), C146.1 (p1), C148.1 (p1), R59.1 (p1), R72.1 (p1), R75.1 (p1), R85.1 (p1), R87.1 (p1), U1.11 (VDDB), U2.11 (VDDB), U3.1 (IN), U3.3 (EN), U14.5 (VDD), U26.1 (p1), U26.3 (p3), U26.20 (p20), U29.3 (VCC), U37.1 (IN), U37.3 (EN); also elsewhere on the board
v15_selv: J4.1 (p1), PS1.4 (VP); also elsewhere on the board
v24_raw: C74.1 (p1), C81.1 (p1), C98.1 (p1), C102.1 (p1), C103.1 (p1), C105.1 (p1), C106.1 (p1), C107.1 (p1), C109.1 (p1), PS2.4 (VP), R62.1 (p1), R128.1 (p1), U26.13 (p13), U26.15 (p15), U26.16 (p16), U41.6 (p6), U41.7 (p7), U42.6 (p6), U42.7 (p7); also elsewhere on the board
vbus_n: J4.12 (p12), U4.6 (VOUTN)
vbus_p: J4.11 (p11), U4.7 (VOUTP)
vdiv_1: R26.2 (p2), R27.1 (p1)
vdiv_2: R27.2 (p2), R28.1 (p1)
vdiv_3: R28.2 (p2), R29.1 (p1)
vsense_in: C27.1 (p1), R29.2 (p2), R30.1 (p1), U4.2 (VINP), U7.4 (INN)
xbleed_mid: R1.2 (p2), R2.1 (p1)

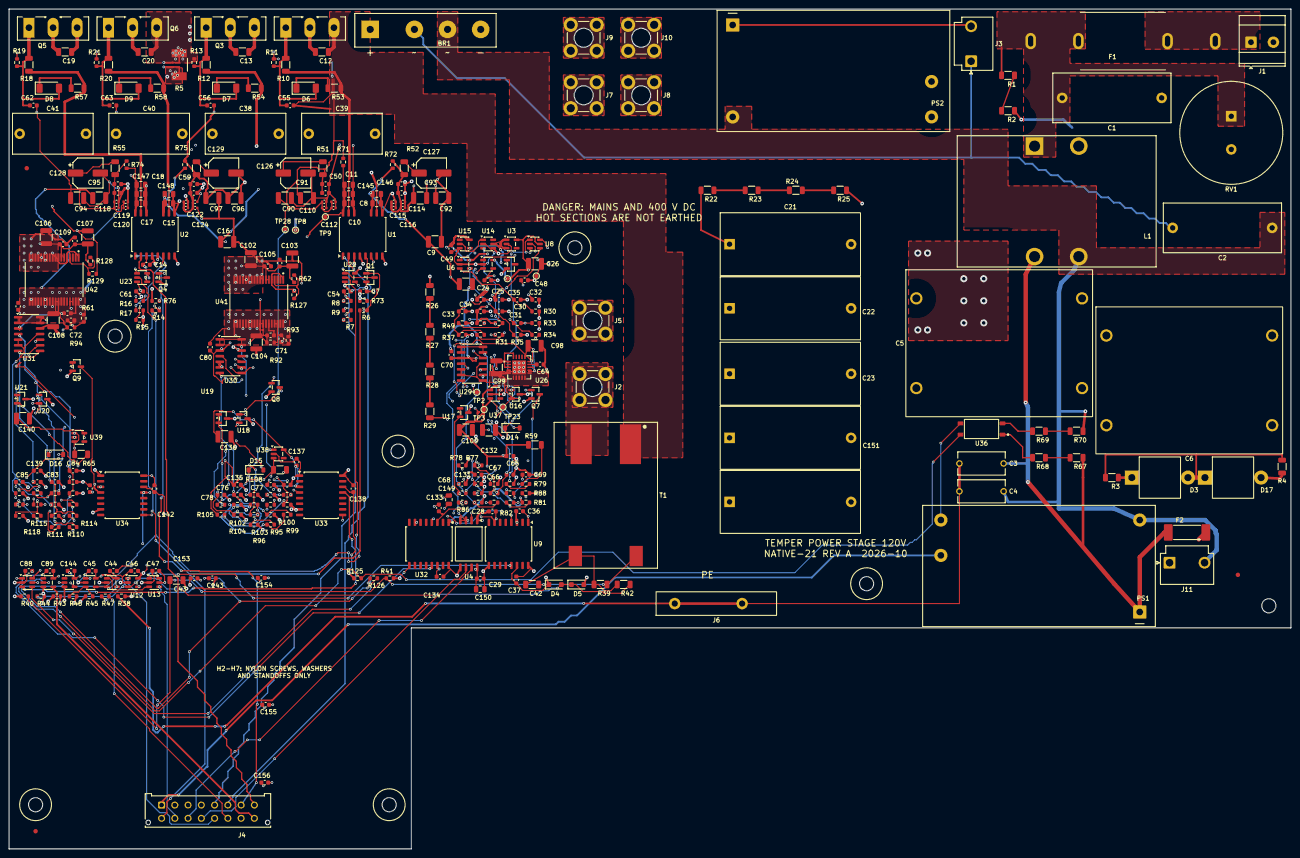
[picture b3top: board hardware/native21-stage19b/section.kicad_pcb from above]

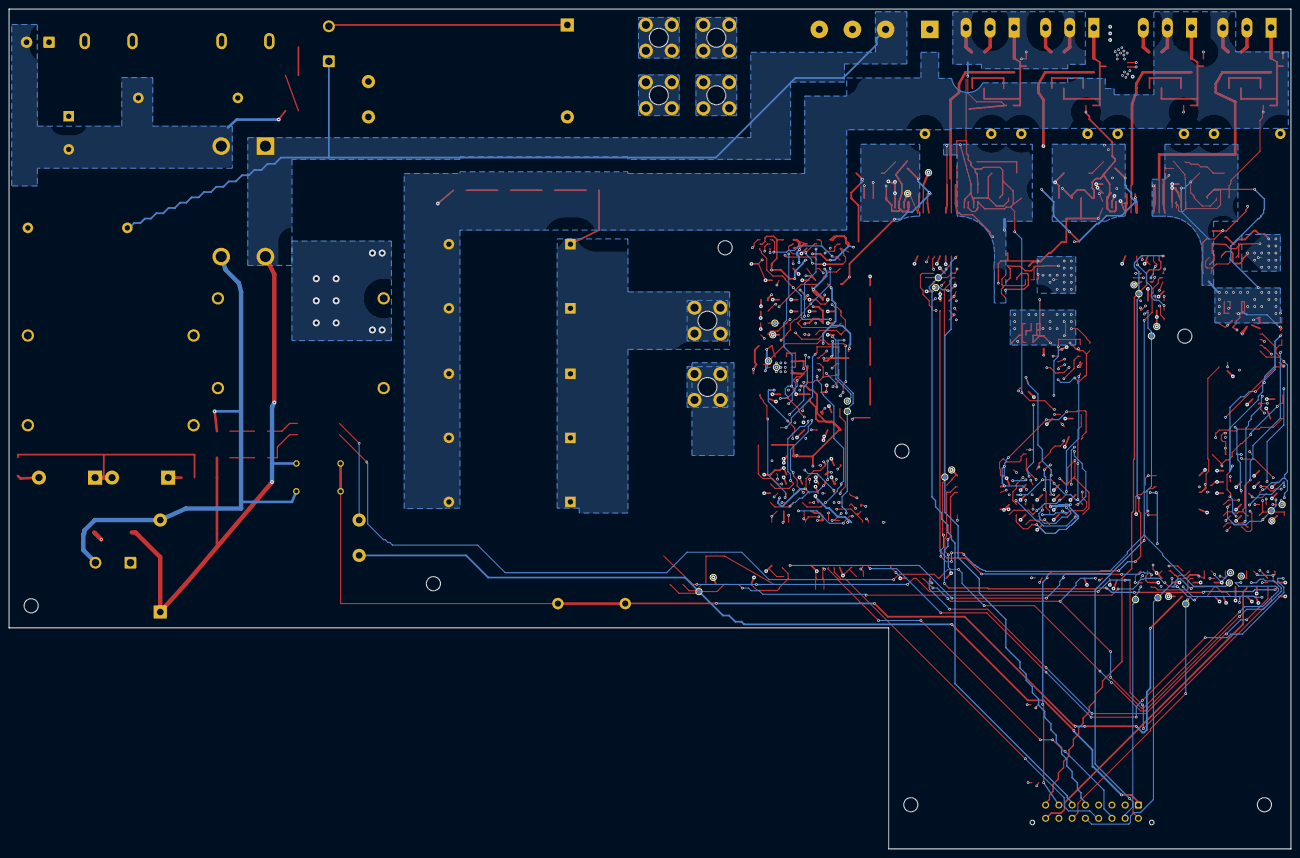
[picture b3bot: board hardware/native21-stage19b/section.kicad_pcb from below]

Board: 4 copper layers, 290.0 x 190.0 mm, 403 parts (28 on the bottom side), 141 nets.

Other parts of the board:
FID1, FID2, FID3: FIDUCIAL; Fiducial_1mm_Mask3mm
H1: M3; MountingHole_3.2mm_M3
H2, H3, H4, H5, H6, H7: M3 NYLON ONLY; MountingHole_3.2mm_M3
TP1: leg_a-out_l; TestPoint_Pad_D1.0mm
TP2, TP22, TP24: n_ls; TestPoint_Pad_D1.0mm
TP3: v15_ls; TestPoint_Pad_D1.0mm
TP4: v24_raw; TestPoint_Pad_D1.0mm
TP5: ocp_node; TestPoint_Pad_D1.0mm
TP6: hot5; TestPoint_Pad_D1.0mm
TP7: bus_fault_hot; TestPoint_Pad_D1.0mm
TP8: n_ha; TestPoint_Pad_D1.0mm
TP9: p_ha; TestPoint_Pad_D1.0mm
TP10: n_hb; TestPoint_Pad_D1.0mm
TP11: p_hb; TestPoint_Pad_D1.0mm
TP12: v15_selv; TestPoint_Pad_D1.0mm
TP13: v3v3; TestPoint_Pad_D1.0mm
TP14: pwm_ha; TestPoint_Pad_D1.0mm
TP15: pwm_la; TestPoint_Pad_D1.0mm
TP16: pwm_hb; TestPoint_Pad_D1.0mm
TP17: permit; TestPoint_Pad_D1.0mm
TP18: bias_bad; TestPoint_Pad_D1.0mm
TP19: bus_fault; TestPoint_Pad_D1.0mm
TP20: ct_zc; TestPoint_Pad_D1.0mm
TP21: ct_mon; TestPoint_Pad_D1.0mm
TP23: leg_ret; TestPoint_Pad_D1.0mm
TP25, TP26, TP27: ocp_kelvin_p; TestPoint_Pad_D1.0mm
TP28: sw_a; TestPoint_Pad_D1.0mm
TP29: sw_b; TestPoint_Pad_D1.0mm
TP30, TP31, TP32, TP33, TP34, TP35, TP36: selv_gnd; TestPoint_Pad_D1.0mm

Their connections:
bias_bad: TP18.1; also elsewhere on the board
bus_fault: TP19.1; also elsewhere on the board
bus_fault_hot: TP7.1; also elsewhere on the board
ct_mon: TP21.1; also elsewhere on the board
ct_zc: TP20.1; also elsewhere on the board
hot5: TP6.1; also elsewhere on the board
leg_a-out_l: TP1.1; also elsewhere on the board
leg_ret: TP23.1; also elsewhere on the board
n_ha: TP8.1; also elsewhere on the board
n_hb: TP10.1; also elsewhere on the board
n_ls: TP2.1, TP22.1, TP24.1; also elsewhere on the board
ocp_kelvin_p: TP25.1, TP26.1, TP27.1; also elsewhere on the board
ocp_node: TP5.1; also elsewhere on the board
p_ha: TP9.1; also elsewhere on the board
p_hb: TP11.1; also elsewhere on the board
permit: TP17.1; also elsewhere on the board
pwm_ha: TP14.1; also elsewhere on the board
pwm_hb: TP16.1; also elsewhere on the board
pwm_la: TP15.1; also elsewhere on the board
selv_gnd: TP30.1, TP31.1, TP32.1, TP33.1, TP34.1, TP35.1, TP36.1; also elsewhere on the board
sw_a: TP28.1; also elsewhere on the board
sw_b: TP29.1; also elsewhere on the board
v3v3: TP13.1; also elsewhere on the board
v15_ls: TP3.1; also elsewhere on the board
v15_selv: TP12.1; also elsewhere on the board
v24_raw: TP4.1; also elsewhere on the board
